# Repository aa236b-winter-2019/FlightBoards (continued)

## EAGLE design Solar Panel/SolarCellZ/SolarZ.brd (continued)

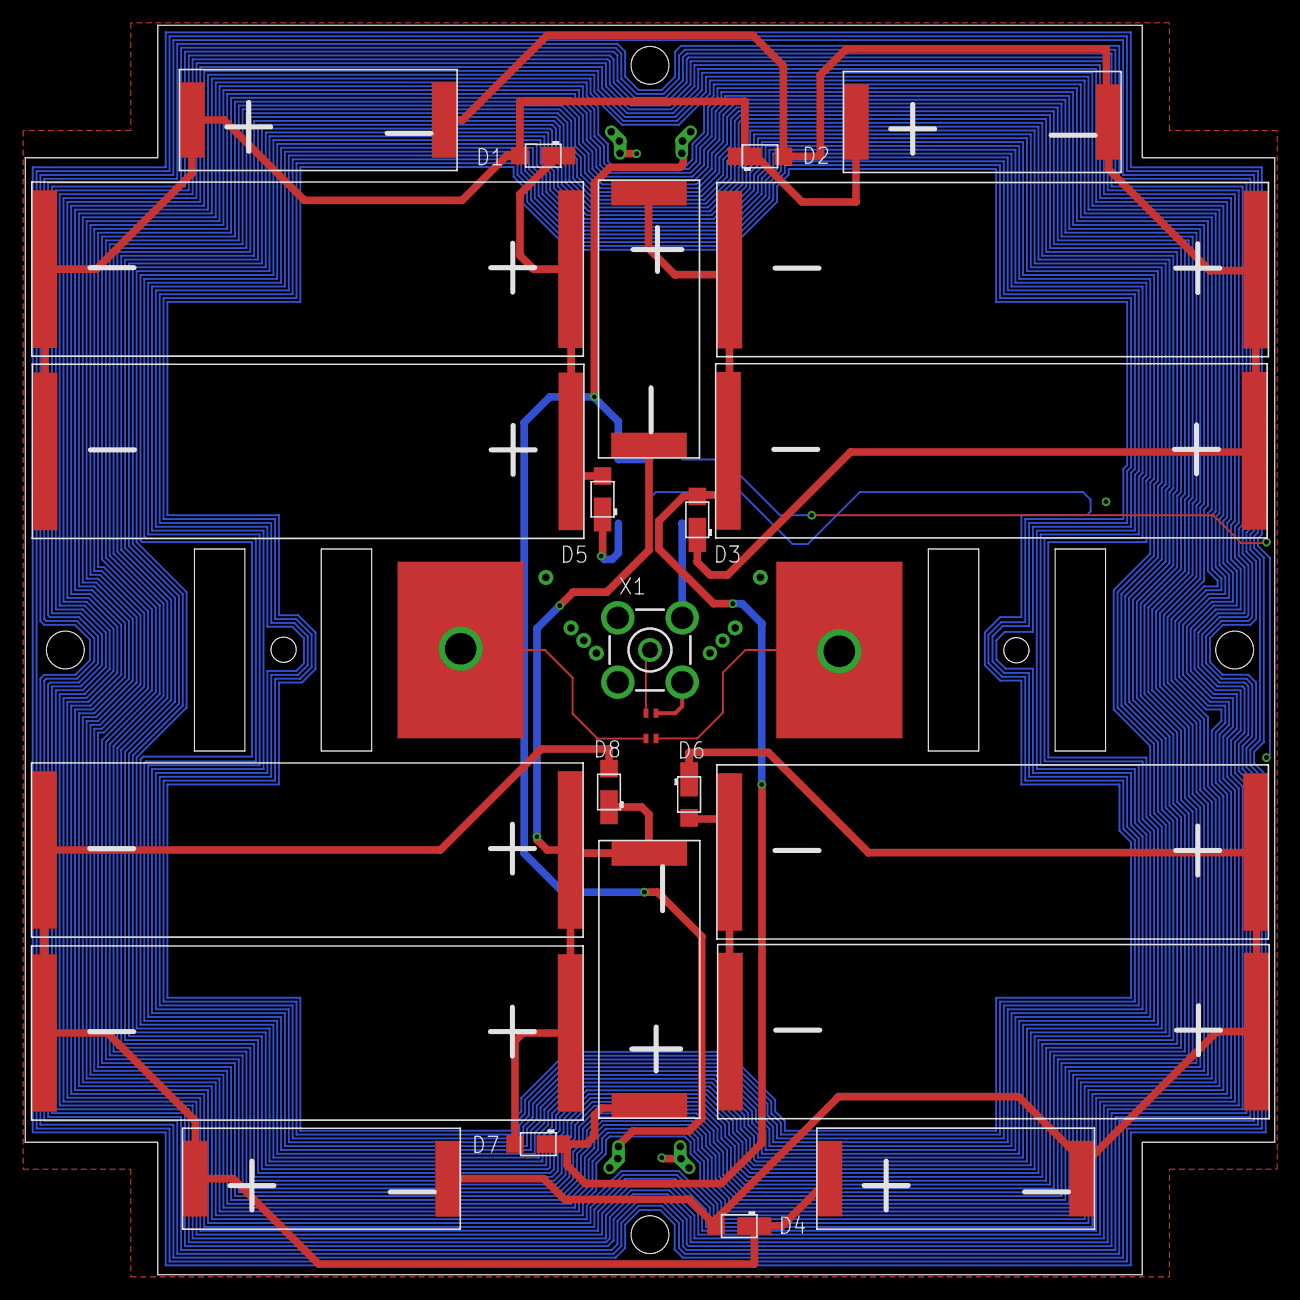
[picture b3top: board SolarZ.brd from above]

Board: 4 copper layers, 99.0 x 99.0 mm, 29 parts (1 on the bottom side), 14 nets.

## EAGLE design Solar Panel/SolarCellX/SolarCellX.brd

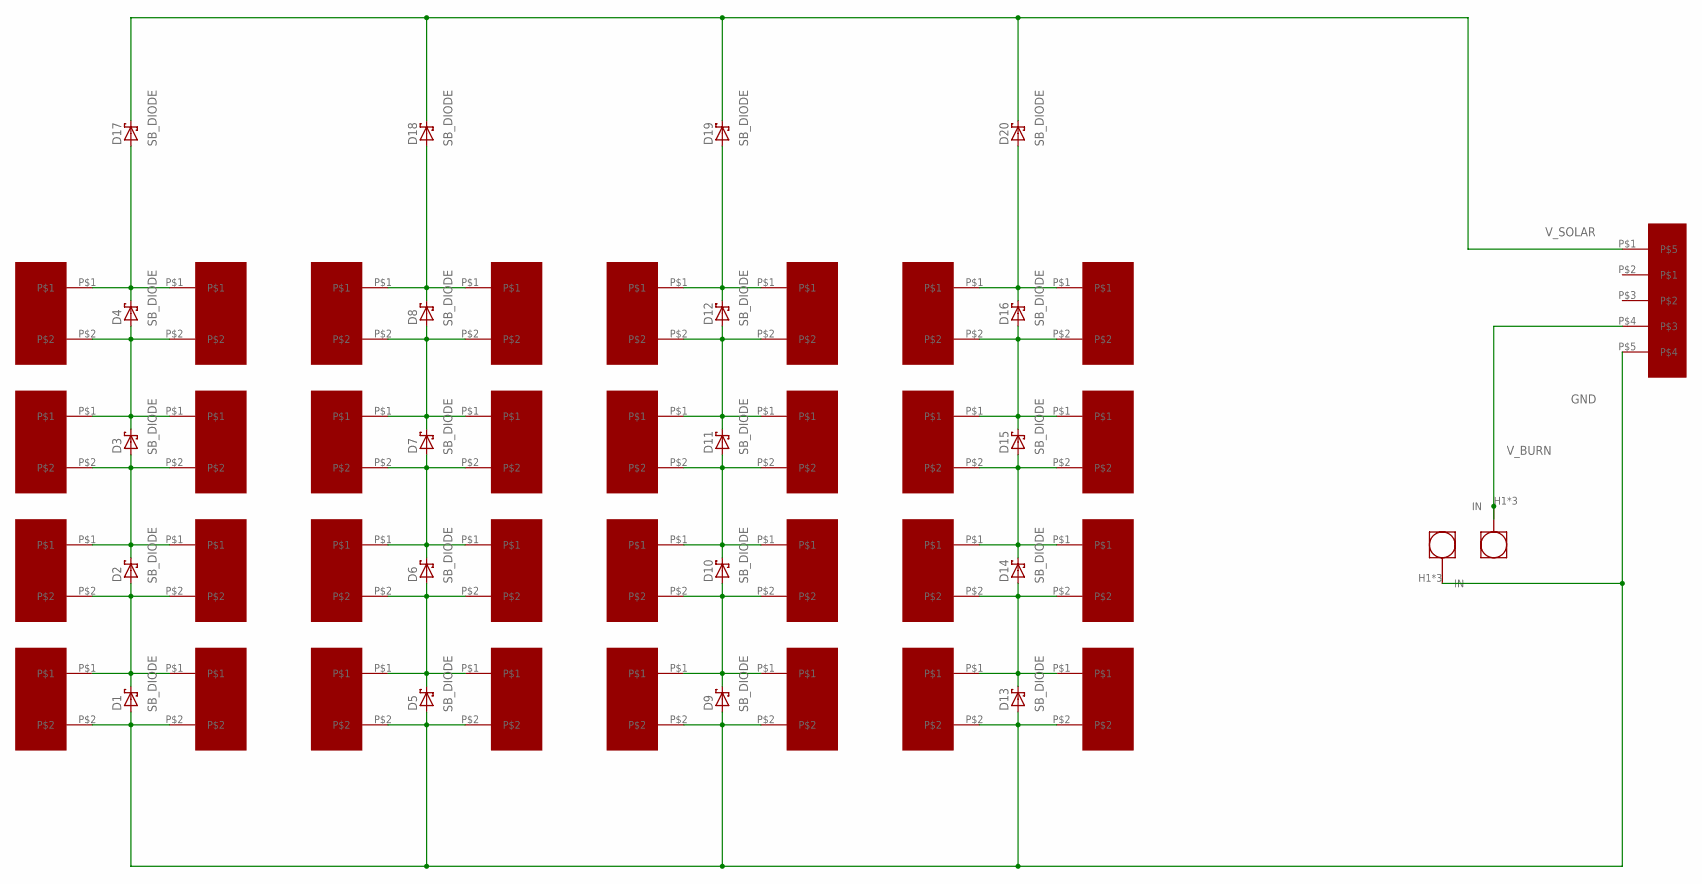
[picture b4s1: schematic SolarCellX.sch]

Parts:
11, 12, 13, 14, 15, 16, 17, 18, 21, 22, 23, 24, 25, 26, 27, 28, 31, 32, 33, 34, 35, 36, 37, 38, 41, 42, 43, 44, 45, 46, 47, 48: KXOB22-04X3F
D1, D2, D3, D4, D5, D6, D7, D8, D9, D10, D11, D12, D13, D14, D15, D16, D17, D18, D19, D20: SB_DIODE
U$33: B5B-EH-A(LF)(SN)
U$34, U$35: BURNER

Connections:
GND: 11.P$2, 12.P$2, 21.P$2, 22.P$2, 31.P$2, 32.P$2, 41.P$2, 42.P$2, D1.POS, D5.POS, D9.POS, D13.POS, U$33.P$5, U$35.H1, U$35.H2, U$35.H3
unnamed: 11.P$1, 12.P$1, 13.P$2, 14.P$2, D1.NEG, D2.POS
unnamed: 13.P$1, 14.P$1, 15.P$2, 16.P$2, D2.NEG, D3.POS
unnamed: 15.P$1, 16.P$1, 17.P$2, 18.P$2, D3.NEG, D4.POS
unnamed: 17.P$1, 18.P$1, D4.NEG, D17.POS
unnamed: 23.P$1, 24.P$1, 25.P$2, 26.P$2, D6.NEG, D7.POS
unnamed: 21.P$1, 22.P$1, 23.P$2, 24.P$2, D5.NEG, D6.POS
unnamed: 25.P$1, 26.P$1, 27.P$2, 28.P$2, D7.NEG, D8.POS
unnamed: 27.P$1, 28.P$1, D8.NEG, D18.POS
unnamed: 31.P$1, 32.P$1, 33.P$2, 34.P$2, D9.NEG, D10.POS
unnamed: 33.P$1, 34.P$1, 35.P$2, 36.P$2, D10.NEG, D11.POS
unnamed: 35.P$1, 36.P$1, 37.P$2, 38.P$2, D11.NEG, D12.POS
unnamed: 37.P$1, 38.P$1, D12.NEG, D19.POS
unnamed: 41.P$1, 42.P$1, 43.P$2, 44.P$2, D13.NEG, D14.POS
unnamed: 43.P$1, 44.P$1, 45.P$2, 46.P$2, D14.NEG, D15.POS
unnamed: 45.P$1, 46.P$1, 47.P$2, 48.P$2, D15.NEG, D16.POS
unnamed: 47.P$1, 48.P$1, D16.NEG, D20.POS
V_BURN: U$33.P$4, U$34.H1, U$34.H2, U$34.H3
V_SOLAR: D17.NEG, D18.NEG, D19.NEG, D20.NEG, U$33.P$1

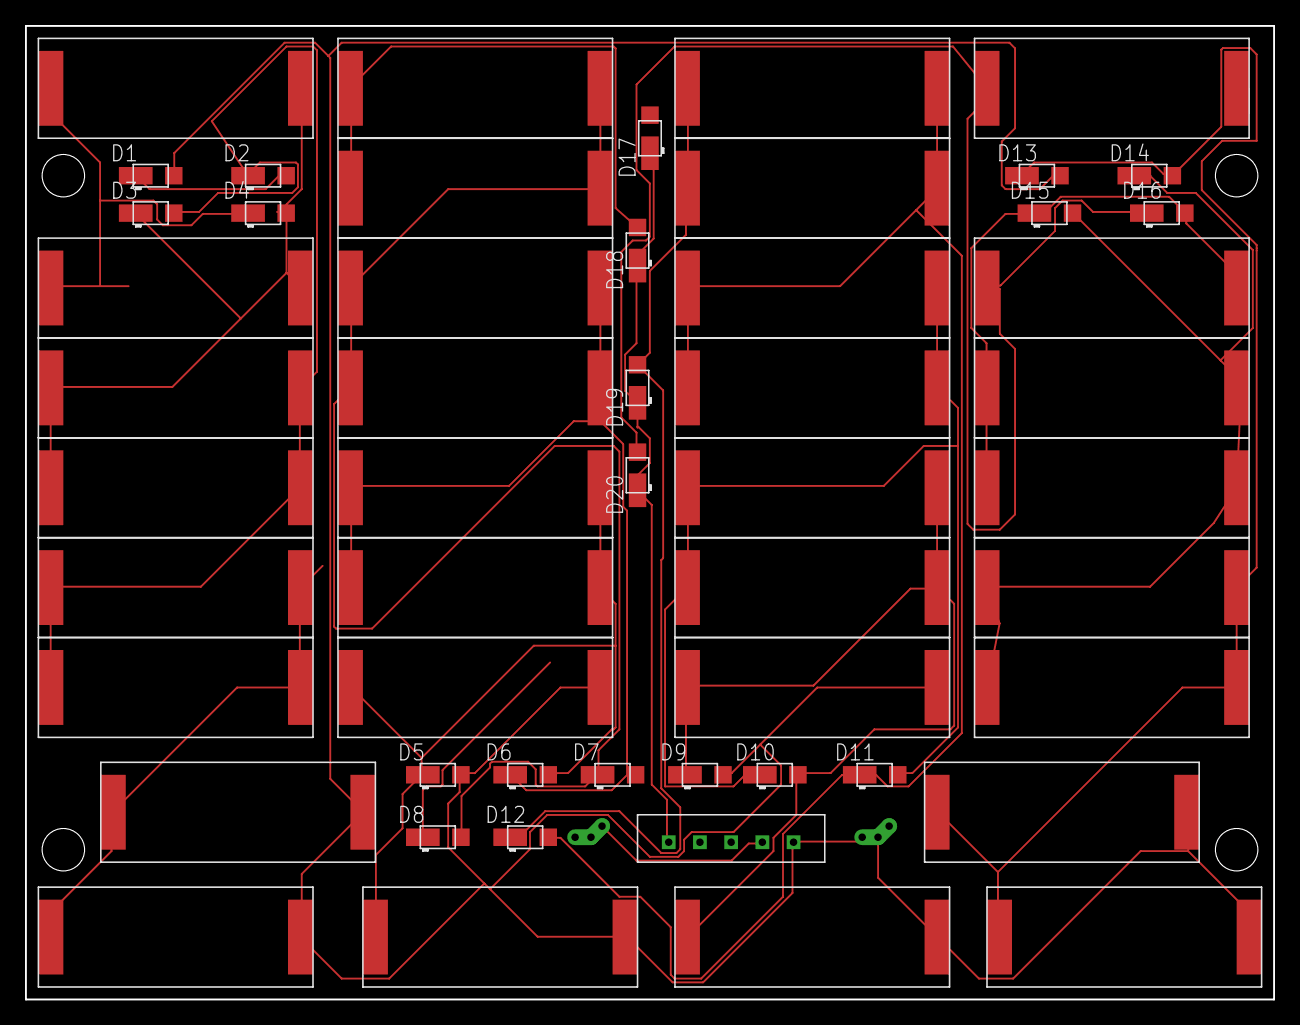
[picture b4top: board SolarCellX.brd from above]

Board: 4 copper layers, 100.0 x 78.0 mm, 55 parts (0 on the bottom side), 19 nets.

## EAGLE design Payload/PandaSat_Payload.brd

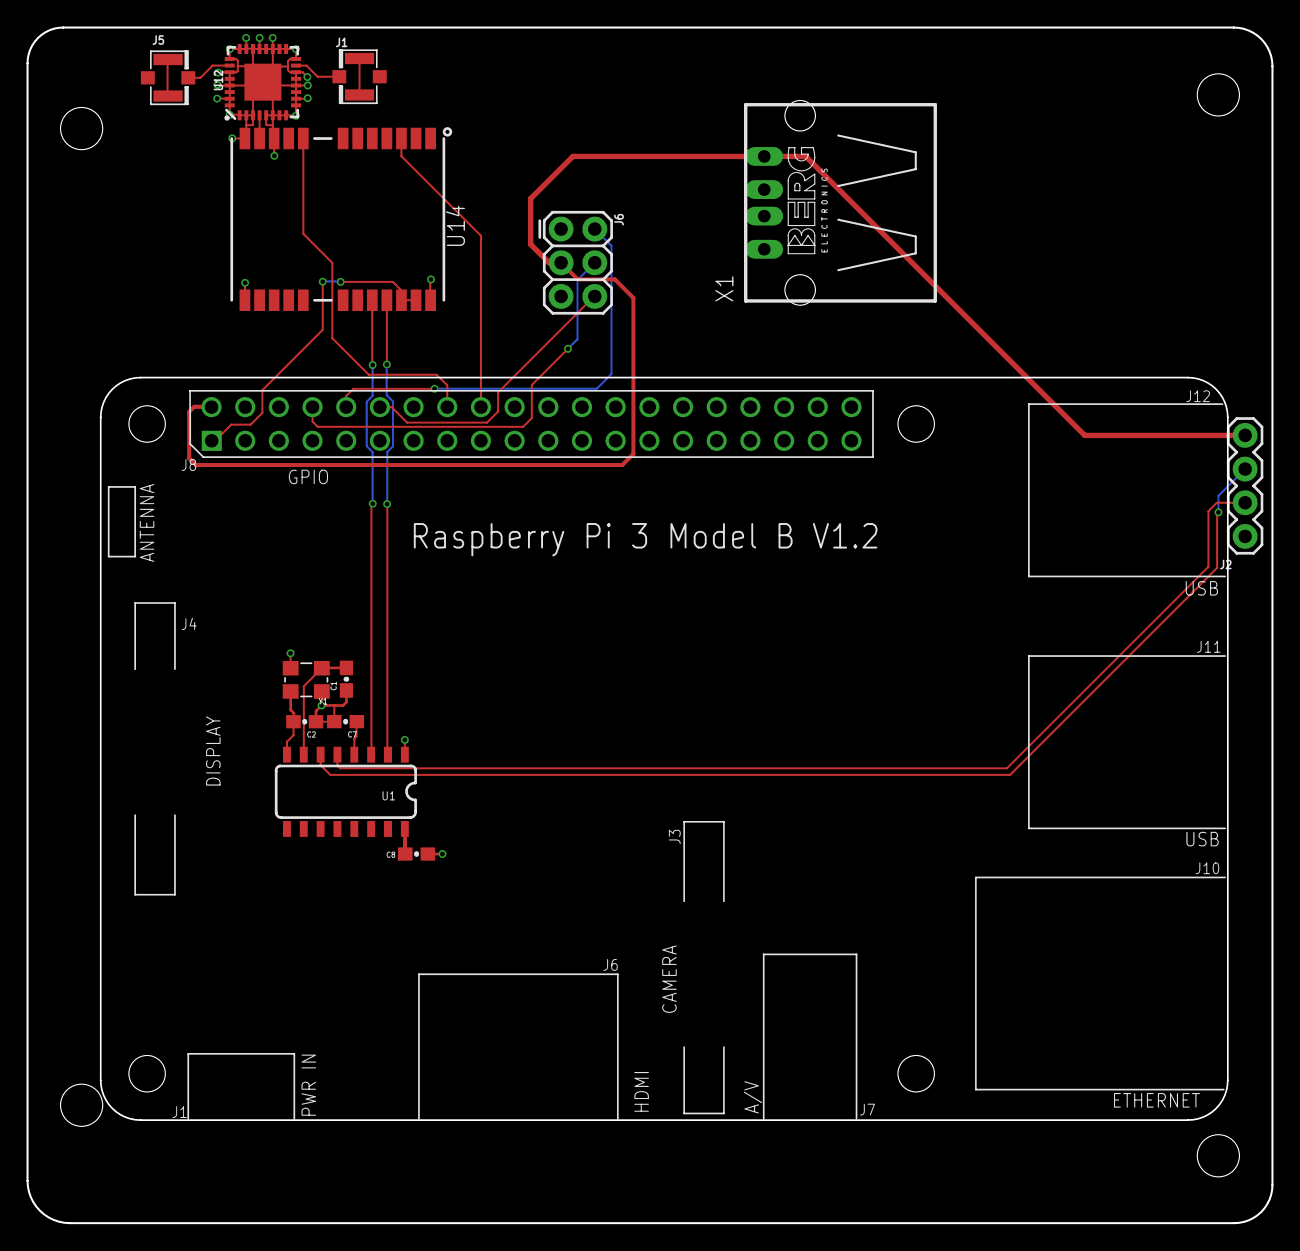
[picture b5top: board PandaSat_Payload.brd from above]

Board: 2 copper layers, 93.9 x 90.2 mm, 16 parts (0 on the bottom side), 21 nets.

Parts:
C1, C2: 10pF; 0603-CAP
C7: 10nF; 0603-CAP
C8: 0.1uF; 0603-CAP
FRAME1, FRAME2: FRAME-LETTERNO_PACKAGE; DUMMY
J1, J5: U.FL
J2: 1X04
J6: FEMALE 2x3; 2X3
PCB1: RPI3RPI3; RPI3
U1: CH340G; SO016
U12: EP2W+; QFN32-5X5MM
U14: S1216V8; S1216_24PIN_PACKAGE
X1: PN87520
Y1: 12MHz; CRYSTAL-SMD-3.2X2.5

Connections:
ENABLE1: J6.6, PCB1.P$12
GND: C1.1, C2.1, C7.2, C8.2, J2.1, J6.1, U1.1, U12.1, U12.2, U12.3, U12.5, U12.6, U12.7, U12.8, U12.9, U12.10, U12.11, U12.12, U12.13, U12.14, U12.16, U12.17, U12.18, U12.19, U12.20, U12.21, U12.22, U12.23, U12.24, U12.25, U12.27, U12.28, U12.29, U12.30, U12.31, U12.32, U12.EP, U14.10, U14.12, U14.13, U14.24, X1.1, Y1.2, Y1.4
GPS_ANTENNA_1: J1.1, J1.2
GPS_ANTENNA_2: J5.1, J5.2
GPS_CLK: PCB1.P$18, U14.3
GPS_RSTN: PCB1.P$16, U14.8
unnamed: C2.2, U1.8, Y1.3
unnamed: C1.2, U1.7, Y1.1
RF_IN: U12.4, U14.11
RXI: U1.3, U14.20
TXO: U1.2, U14.21
U.FL1: J1.FEED, U12.15
U.FL2: J5.FEED, U12.26
UART2_RX: J6.2, PCB1.P$10
UART2_TX: J6.4, PCB1.P$8
UD+: J2.2, U1.5
UD-: J2.3, U1.6
V1: C7.1, U1.4
VCC: C8.1, U1.16
VCC3.3: PCB1.P$1, U14.22, U14.23
VCC5: J2.4, J6.3, PCB1.P$2, X1.4

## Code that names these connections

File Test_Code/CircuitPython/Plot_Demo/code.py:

# Read Data from IMU

import microcontroller
import digitalio
import time
import busio
import adafruit_lsm9ds1

# Setup I2C bus and sensor
SDL = microcontroller.pin.PA12
SCL = microcontroller.pin.PA13
i2c  = busio.I2C(SCL,SDL)
sensor = adafruit_lsm9ds1.LSM9DS1_I2C(i2c)

# Setup LED
led1 = digitalio.DigitalInOut(microcontroller.pin.PA09)
led1.direction = digitalio.Direction.OUTPUT
led2 = digitalio.DigitalInOut(microcontroller.pin.PA10)
led2.direction = digitalio.Direction.OUTPUT
led3 = digitalio.DigitalInOut(microcontroller.pin.PA11)
led3.direction = digitalio.Direction.OUTPUT

count = 0

while True:
    # Read acceleration, magnetometer, gyroscope, temperature.
    accel_x, accel_y, accel_z = sensor.acceleration
    mag_x, mag_y, mag_z = sensor.magnetic
    gyro_x, gyro_y, gyro_z = sensor.gyro
    temp = sensor.temperature

    #Print acceleration data for mu plotter
    print((accel_x,accel_y,accel_z))
    time.sleep(0.05)

    count = count+1

    if count < 10:
        led1.value = True
        led2.value = True
        led3.value = False
    elif count < 20:
        led1.value = False
        led2.value = True
        led3.value = True
    elif count < 30:
        led1.value = True
        led2.value = False
        led3.value = True
    else:
        count = 0

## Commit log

2019-01-17 Started work on side solar panels
2019-01-22 Added useful Motherboard schematic (empty) and useful libraries including custom ATSAMD51
2019-01-23 Changed most of major components from KickSat to fit PandaSat
2019-01-23 Added datasheets
2019-01-23 Put charging circuit back in
2019-01-23 First rough pass at solar board
    This rough board only includes the panels, the burn wire, and the connector so far
2019-01-23 5V Power Circuit .. in progress
2019-01-24 Updated Watchdog timer & 5V reg
2019-01-24 More mobo schematic work incl Hbridge, battery and regulator circuitry
2019-01-24 Rearranged schematics and added payload connection
2019-01-24 Updated Samd51 symbol, Changed Battery config to 2s2p, Added Power + Osc to MCU
2019-01-24 Changed diode on power jack
2019-01-24 Added I2C and WDT Interface
2019-01-25 Updated Solar Panel with Alex's new sizes
2019-01-25 Updated solar cell with larger solar panels
2019-01-25 Fixed H-Bridge circuits
2019-01-25 Added LEDS, Added decoupling Caps for MCU, Labeled Analog Pins
2019-01-25 Added Todos, testing Slack notification
2019-01-28 Replaced 4-pin payload connector with 6-pin connector
2019-01-28 Routed communication lines and analog signals, changed 5V regulator circuit
2019-01-28 aesthetic changes
2019-01-28 Added passives to H-Bridges
2019-01-29 Swapped Datasheets
2019-01-29 Edits to Solar cell
2019-01-29 Added level shifting circuits, added in proper diodes and PFETs, finished routing digital circuitry, changed connectors
2019-01-29 Added test points
2019-01-31 Set Up PCB stack up , created board outline and PC104 mounting holes
2019-01-31 SolarCell X first complete revision
2019-01-31 Widened traces on solar board and shuffled
2019-01-31 Changed battery charge circuit, added caps on 3V3 reg input, removed logic level shifting circuit, removed diode on solar panel input
2019-01-31 Changing connectors to SMD - not yet netted
2019-02-01 Finished with schematic, began placing components
2019-02-01 6mil magnetorquer trace updated
    Barrel jack added
2019-02-01 Reviewed solar panel board
2019-02-01 Reviewed solar panel board - DRC
2019-02-01 Changed the Connector cutout profile to give some wiggle room for tolerances
2019-02-02 More component placing - power componente
2019-02-02 Finalized board and gerber files finished
2019-02-02 *Trimmed a mm from long side of PCB *Started Arranging Parts on Board
    Todos:
    Find Parts on Digikey/Mouser and add to BOM spreadsheet [in Documentation BOM]
    Change Footprint on Crystal to SMD [Part in Documentation BOM]
    Verify Footprints of Parts vs parts selected on BOM [package, Pad Sizes, Pin 1 label]
    Change Diode Symbols [3 on Battery Connections]
    Change Foot Print of all 0603 parts to be same one [ Hand solder-able Dimensions] & also other size of passives
2019-02-02 * Did Some initial Layout and found a few tasks to do [Listed in Commit Message] Trimmed a mm from long side of PCB Started Arranging Parts on Board
    Todos:
    Find Parts on Digikey/Mouser and add to BOM spreadsheet [in Documentation BOM]
    Change Footprint on Crystal to SMD [Part in Documentation BOM]
    Verify Footprints of Parts vs parts selected on BOM [package, Pad Sizes, Pin 1 label]
    Change Diode Symbols [3 on Battery Connections]
    Change Foot Print of all 0603 parts to be same one [ Hand solder-able Dimensions] & also other size of passives
2019-02-03 Changed several components to fit BOM
2019-02-04 Added gerbers
2019-02-04 Changed all caps to 0603, need to change to all same part so text size is consistent
2019-02-04 A bunch of Routing
2019-02-04 moved parts
2019-02-04 Eagle and Git were not getting along
2019-02-04 Is this gonna work?
2019-02-05 More arranging
2019-02-05 Changed caps, added new inductor parts, removed fuse
2019-02-05 Added USB Bypass
2019-02-05 Switched Barrel Jack to smd Changed Footprints for 2x3 conn to include casing Changed Hbridges to pair x&z instead of x&y fixed mislabeled net PL_PWR_EN -> PL_PWR_ENAB
    Did all the signal routing, just need 5V and 3.3V
2019-02-06 Finished?!? Rev 1 Routing - DRC < 50 Messages
    Also Added Grnd and Power planes
    Need to Fix LED foot print
    Fix Weird VBatt Node
2019-02-07 took out extraneous board designs
2019-02-07 Fixed Mounting Hole misalignment and Passing DRC
2019-02-07 Added Height attribute motherboard parts
2019-02-07 Added CAD model of motherboard
2019-02-07 Corrected foot/rail switch parts
2019-02-07 Added mounting holes to MB CAD model
2019-02-08 Moved Usb Cable
2019-02-08 Moved Solar Panels to have Space for mounting hardware
2019-02-08 Updated schematic and MB as per meeting
2019-02-08 Fixed??? Solar Panel X Final + MB
2019-02-08 Fixed pt2
2019-02-08 Fixed last real DRC errors
2019-02-08 Re-added schematic frames
2019-02-08 Added 3d part models
2019-02-08 Added CircuitWorks Files
2019-02-08 Rounded corners, added Logo
2019-02-08 Solar Panel Gerbers Final X, DRC updates for MB
2019-02-09 Updated DRC Rules and fixed up errors
2019-02-09 DRC error fixes, changed footprint for USB-C w/ milling layer
2019-02-11 Finished first pass of solar cell Y with GPS cutout
2019-02-11 Changed connector config and DRC stuff for Y panel
2019-02-11 Fixed Silkscreen for Solar Y, Upload Rev A gerbers.
    Sent to BAC:
    PandaSat_MB_RevA4.zip
    SolarCellX_v2_6milmag_RevA.zip
    SolarCellY_v2_6milmag_RevA.zip
2019-02-11 Added Payload Board to Flightboards Repo.
2019-02-11 Flipped FTDI circuitry to allow access when Pi installed, addedconnector for USB passthrough from MB
2019-02-12 Finalized Y and created gerbers
2019-02-12 redid some spacing
2019-02-12 Updated MB 3d CAD model
2019-02-12 Moved CAD Folder
2019-02-12 Changed footprint of LTC4121
2019-02-14 Began Z panel
2019-02-14 Routing on draft Z panel - dimensions need to be confirmed
2019-02-14 Some Magnetorquer routing
2019-02-15 Magnetorquers done
2019-02-15 Added solarZ 3D model
2019-02-16 Added space around cutouts
2019-02-19 Changed RF trace width
2019-02-20 Resolved a diode issue on SolarCellX and pushed new gerber
2019-02-25 Changed Z panel hole
2019-02-25 Solar Z Panel done passing all DFM checks
2019-02-26 Added Solar-Y CAD model
2019-02-27 Updated schematic + layout but have some git troubles!
2019-02-27 Fixed lib issue
2019-02-27 Some MB updates + X Panel CAD update
2019-02-27 Updates to MB
2019-02-27 Added polarity to solar panel package
2019-02-27 Readded frames on schematics
2019-02-27 Updated 3D solar models
2019-02-27 Added solar cell depth
2019-03-01 Updated to use new solar cell library footprint
2019-03-03 Re-routed traces internally, changed USB-C for Mini USB and changed 5V enable circuit
2019-03-03 Changed text to Rev B
2019-03-03 Added CircuitPython files
2019-03-03 Minor Edits to layout, Ground + Power Floods, Added Names. Maybe Ready?
2019-03-03 Spelling
2019-03-04 Cleared more room around bottom battery mounting holes:
2019-03-04 Rev 2 Silkscreen
2019-03-04 Added DataSheet for button
2019-03-12 Moved magnetorquers and shrunk outside of Z board
2019-03-12 Changed pinout for X, added silkscreen
2019-03-12 Updated circuit python code
2019-03-12 Ground pour for X panel and silkscreen changes for z
2019-03-12 minor rerouting
2019-03-12 Clearance fixes for X plus gerber generation
2019-03-15 Silk Screen Fixes
